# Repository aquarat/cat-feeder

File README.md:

# Cat feeder

An easy-clean, screwless, refrigerated rotary feeder. **Early mechanical and
thermal prototype**, developed from [the original brief](initial-design-brief.md)
and the owner's subsequent decisions in [the project KB](kb/README.md).

Twelve 40 mL portions sit in a lift-out tray. A stepper advances the tray 30°
at a time under a fixed opening in the lid. Thermoelectric coolers chill the
air beneath the tray. The lid hinges open and the tray lifts out for washing
without tools. The prototype is printed in PETG on a Bambu A1 Mini.

| | |
|:---:|:---:|
|  |  |
| **Opened:** twelve compartments in four lift-out sectors on a keyed hub | **Exploded:** lid, tray, plenum deck and body |
|  |  |
| **Section:** tray over the cold-air plenum and equipment bay | **Internals (deck hidden):** TEC stacks, [controller cards](electronics/d34/README.md) and modelled harness |

<p align="center">
  
  <br><em>D34 control card, one of three hand-soldered through-hole boards.</em>
</p>

*These are renders of the CAD model for the
[cold-air plenum study](kb/plenum-cad.md) (D35, still being compared). They
are not photographs: nothing has been built or tested yet. Refresh them with
`bash scripts/export_plenum.sh && bash scripts/readme_images.sh`.*

**[Product-linked BOM](BOM.md)** — UK-oriented sourcing, trial/full quantities,
observed prices and fit dependencies. Start with one thermal wedge; see the
[sourcing evidence](kb/sourcing.md) for outstanding component choices.
The [TEC control recommendation](kb/tec-control.md) identifies a CP60440 sample
and DPS5005 bench regulator, with conditional three-series/four-parallel scaling.
The [PCB assembly review](kb/pcb-assembly.md) recommends JLCPCB Economic as the
first turnkey controller-board route. The [crescent controller draft](kb/pcb-design.md)
has passed independent review.
The [PCB supports and removable sink cradles](kb/pcb-packaging.md) are integrated.
Subsequent [electrical simulations and regression tests](kb/pcb-simulation.md)
identify regulator thermal, motor-supply ringing and interface limits requiring
qualification; no powered hardware or application firmware has been tested.

> **2026-10-25:** a [five-reviewer general review](kb/review-2026-10-25.md) found
> blockers in both PCB revisions and thermal/drag limits in the direct-contact
> concept. Do not quote the prepared JLCPCB project. Latest decisions: 24 V
> mains brick, electronics inside the case, a hand-soldered through-hole
> controller variant, and an exploratory cold-air plenum
> ([thermal](kb/plenum-thermal.md), [CAD study](kb/plenum-cad.md), [sizing](kb/plenum-sizing.md); [D32–D37](kb/decisions.md)). D34 controller cards:
> [electronics/d34](electronics/d34/README.md), [KB](kb/d34-controller.md).
> Plenum views: `bash scripts/export_plenum.sh` → `build/plenum/preview/`.

## Current direction

- **316 mm nominal body**, 280 mm rotating tray, twelve 40 mL working portions.
- Four lift-out tray quadrants, three rounded wedge bowls each. Every bowl is
  continuous; joins are outside the food cavities. Nominal floor **1.2 mm**,
  bowl depth **16 mm**, plan corner radius **5 mm**, floor fillet **3 mm**.
- A broad, uniquely keyed **axial drive coupling** on the stepper. Lift the
  carrier and tray straight off; no shaft screw, nut or fastening operation.
  This resembles a large gear but does not provide gear reduction.
- Rear pin hinge and **one front-right clip** reuse the rowing IMU mechanisms.
  Filament offcuts form the pins. The enlarged lid needs its own load/fit trial.
- **18 mm printed insulation deck**, low-infill enclosed construction; no foam.
- **Domed lid with a broad, gently sloping feeding recess**. The mouth edge
  stands just 2.8 mm above the tray rim. The rest of the lid grows thicker.
- **12 mm cylindrical walls**, with honeycomb specified by Bambu print settings.
  CAD describes the envelopes; there are no modelled honeycomb cavities.
- **Enclosed, slotted underside** and numerous narrow vertical side vents.
  Floor-rooted seats, guides and bounded electrical bays load from the top.
- **Twelve distributed cooling positions**, one beneath each parked portion,
  replacing the custom circular aluminium plate. The current layout reserves
  40 mm TECs directly contacting the PETG tray and individual heat sinks. Final TEC size,
  count and power depend on the thermal study and a single-position experiment.
- One common fan and local thermostatic control. The original 100 W USB-C supply
  remains a candidate, not a proven budget for this revised cooling layout.
- Bottom **120 mm upward-blowing axial fan**, with a printed inlet skirt,
  enlarged floor intake and raised side exhaust band. See [airflow study](kb/airflow.md).

## Files and views

| File | Purpose |
| --- | --- |
| `cad/parameters.scad` | Dimensions, provisional component envelopes and clearances |
| `cad/feeder.scad` | Parametric assembly, section, exploded view and prototype parts |
| `cad/internals.scad` | Floor supports, removable motor bridge, board bays and loading paths |
| `cad/pcb_mount.scad` | Crescent PCB edge seat, lift-out sink cradles and staged loading paths |
| `docker/openscad.Dockerfile` | Headless build of the pinned public OpenSCAD fork |
| `scripts/openscad.sh` | Run OpenSCAD in that Docker image, with this project mounted |
| `scripts/fetch_references.py` | Fetch the manufacturer datasheets listed in `references.json` |
| `scripts/export.sh` | Export prototype STLs and current PNG views |
| `scripts/check_mesh.py` | Actual mesh topology, connectedness, bed fit and bowl capacity |
| `kb/` | Decisions, evidence, open questions and handover notes |
| `thermal/` | Thermal modelling tools and their results |
| `slicer/` | Editable Bambu project plate generation and print settings |
| `cad/lib/` | Hinge/clip mechanisms and edge helpers vendored from upstream ([provenance](#provenance)) |

Generated outputs are in `build/stl/`, `build/preview/` and
`build/geometry-report.json`. `capacity.stl` is the **empty volume of one bowl**
for measurement, not a printable part. Colours in assembly views distinguish
components; the rectangular heat sinks and fan are packaging envelopes.

[Opened assembly](build/preview/opened.png) ·
[Section](build/preview/section.png) ·
[Feeding recess](build/preview/access.png) ·
[Component bays](build/preview/loading.png) ·
[Underside](build/preview/underside.png) ·
[Fan inlet coupon](build/preview/fan_inlet_coupon.png)

The bowl capacity is **53.20 mL**. The full lid and shell remain assembly-scale
models requiring printable subdivision. See [validation details and limits](kb/validation.md)
for the tested revision and [the drop-in layout](kb/drop-in-layout.md) for assembly order.
The current thirteen prototype meshes and 44 nominal clearance checks pass; eleven
editable, unsliced Bambu projects are available in [slicer/plates](slicer/plates/).
The PCB fit study adds 21 passing checks against the integrated shell.

The [earlier thermal study](kb/thermal-model.md) identifies lateral heat spreading
as an unresolved issue with small cold footprints. The latest prototype removes
the small aluminium caps and tests direct TEC-to-PETG contact. Start with one
instrumented wedge and its insulated cover before scaling to twelve sites.
The [direct-contact comparison](kb/direct-contact-thermal.md) finds only about
0.3–0.4°C higher mean food-layer temperature without the small caps under matched
ideal cold-face conditions; contact gaps matter more. These are simulations.

## Reproduce

The CAD scripts run a headless OpenSCAD in Docker. Build the image once
(20–40 minutes; it compiles the pinned
[public OpenSCAD fork](https://github.com/aquarat/openscad), which adds the
experimental `geometry-metrics` checks):

```sh
docker build -t cat-feeder-openscad -f docker/openscad.Dockerfile docker
```

Manufacturer datasheets are not redistributed. Fetch them to the paths the
documentation cites (hash-checked against the revisions used):

```sh
python3 scripts/fetch_references.py
```

Export and check:

```sh
bash scripts/export.sh
python3 scripts/check_mesh.py
bash scripts/check_clearances.sh
python3 slicer/make_plates.py --require-part lid_access_coupon --require-part motor_bridge --require-part fan_inlet_coupon --require-part pcb_cradle --require-part pcb_mount_coupon
python3 slicer/make_plates.py --verify-only
```

Editable **unsliced** Bambu projects are written to `slicer/plates/`. Open them
as projects and retain their settings, then slice in Bambu Studio. No GUI or
slicer executable is required to generate these files here; no print G-code
is claimed. See [printing notes](kb/printing.md).

For one part or a parameter variation:

```sh
mkdir -p build/stl
bash scripts/openscad.sh --backend=Manifold --export-format binstl \
  -D 'part="sector"' -D 'floor_t=1.6' \
  -o build/stl/sector-thicker.stl cad/feeder.scad
```

## Prototype print order

1. **One tray sector**: check 40 mL filling, cat access, leakage and cleaning.
   Print flat underside down. The dry inner flange is on the bed too.
2. **Drive and hub**: check the measured motor shaft, master-tooth engagement,
   vertical removal and torque. Nominal sliding clearance is 0.3 mm per side;
   the provisional 5 mm D shaft has a separate close fit. The drive's blind
   socket seats on the shaft tip, its shoulder supports the hub, and two tabs
   provide a finger grip. The motor envelope assumes a 28 mm body/18 mm shaft.
3. **Rowing closure coupons and clip**: reproduce the actual hinge/catch
   interfaces. These are upstream coupons, not a full-size lid strength test.
4. **One insulation quadrant**: cold face down, as exported. Start with
   0.8 mm skins and 5–8% infill; inspect closure of the infill and print accuracy.
   This is a packaging coupon; module retention and moisture detailing follow
   the selected cooling cartridge.
5. **Insulation coupon**: a plain 60 mm square envelope. Apply the Bambu
   honeycomb/skin settings and inspect the generated infill and roof layers.
6. **Feeding-access coupon**: the actual front section of the sloped lid,
   including its thin opening lip. Check access and whisker clearance over a tray.
7. **Motor bridge**: its 2 mm bearing lip sits 1 mm above the fan; check seating
   on the four floor posts and the actual motor before a full loaded build.
8. **Fan-inlet coupon**: trial the actual enlarged floor slots, 2 mm-high inlet
    skirt and corner seats with the selected 120 mm fan before printing the shell.
9. **PCB mount coupon and two cradles**: check the edge seat, locating sockets,
   actual solder tails and driver stack. The cradle project contains one copy;
   print two for the assembly. Connect terminal wires after seating the PCB.

PETG, 0.4 mm nozzle and 0.2 mm layers are the initial process assumptions.
Use solid floors/perimeters on food parts; low infill applies to insulation,
not liquid-retaining walls. Rounded geometry helps washing, but does not by
itself establish FDM surface cleanability or food-contact suitability. Treat
these as water/fit prototypes until the material and cleaning process are settled.

## What is modelled versus resolved

The tray, drive, closure coupons, feeding-access coupon and removable motor
bridge have exportable prototype geometry. Mesh checks establish printable size
and closed surfaces, not physical fit, lifetime or liquid tightness.

The **full shell and lid are assembly studies**, not final A1 Mini prints.
Their quadrant joints, full-size lid support/stop, anti-lift retention, fan duct,
indexing sensor, condensate management and cartridge clamps still need detail.
Bounded electronics bays and floor-supported component seats are present. The
crescent uses its actual PCB outline with provisional component/harness heights;
the other three pockets remain unselected module allowances. The deck needs final quadrant joining and
cartridge retention features. Final hardware dimensions and firmware pinout
are not frozen.

The direct-contact prototype needs repeatable TEC face height and hot-side
contact with its sink. The deck carries the tray around each exposed cold face;
physical flatness/contact and sliding drag need a trial. Small aluminium caps
are removed. A proven long-life spring clamp is not a prerequisite for testing
the concept, but the final hot-side retention method remains to qualify.

Daily operation should be: release the clip, open lid, lift the complete tray by
its carrier, separate quadrants for washing/refilling, reseat and close. The
hub's unique key restores mechanical phase; starting a new food batch must
still reset the serving count. The four identical tray quadrants can otherwise
be exchanged, so lifting/reloading during an active batch requires rechecking it.

## Provenance

`cad/lib/` holds three OpenSCAD files vendored from the author's rowing-computer
project, unchanged apart from include paths: `sensor.scad` (the rear pin hinge
and clip mechanisms, rowing revision `5eb1d5683712bf8eaba0b004c4f59e09f8ab5160`)
and `edges.scad`/`dfm.scad`, which are also published in the
[OpenSCAD fork](https://github.com/aquarat/openscad) at
`12b187123519cd9050ce37341aefaa3e31ced1f7`.

This repository is a published snapshot of the project's working repository.
Issues and pull requests are welcome; accepted changes are applied upstream
and appear here in the next snapshot.

## Licence

Copyleft throughout: CERN-OHL-S-2.0 for hardware designs, GPL-3.0-or-later for
software, CC-BY-SA-4.0 for documentation, plus third-party AGPL/SparkFun files.
See [LICENSE.md](LICENSE.md). This is an untested prototype; no warranty.

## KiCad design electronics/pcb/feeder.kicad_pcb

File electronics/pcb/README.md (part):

# Cat-feeder controller — revision A draft

Editable **KiCad 9** schematic and fully connected, two-layer **shallow crescent PCB, 58.12 × 80 mm bounding box**. Actual area is only **2.17% above the 50 × 80 mm rectangular baseline**. This is a checked design draft, not a fabricated/tested controller. Start with [packaging assumptions/comparison](PACKAGING.md), [design rationale](../../kb/pcb-design.md) and [check results](CHECKS.md).

**D25 HOLD: review corrections are ready for focused independent recheck; supplier-project creation remains prohibited.** [Precise B1/B2/rule-fix record](REVIEW-FIXES.md). Current revision adds R20/R21; all original placements and the outline are preserved.

## Files

| File | Purpose |
|---|---|
| `feeder.kicad_pro`, `feeder.kicad_sch`, `feeder.kicad_pcb` | Open the project in KiCad 9; current editable design |
| `feeder.pretty/`, `fp-lib-table`, `sym-lib-table` | Local footprint copies; schematic embeds its symbols and references standard KiCad 9 symbol libraries |
| `views/schematic.pdf`, `views/feeder.svg` | Current schematic; net-labelled pin stubs carry the electrical connections |
| `views/top.svg`, `views/bottom.svg`, `views/assembly.svg` | Current copper/component views; bottom view is **not mirrored**, seen through the board from above |
| `views/board-only.step`, `views/board-envelope.stl`, `outline-study.json` | Curved-outline mechanical handoff; coordinate systems and omitted geometry in [PACKAGING.md](PACKAGING.md) |
| `design-bom.csv`, `connectivity.json`, `schematic-netlist.xml` | Full design BOM and connectivity |
| `assembly-bom.csv`, `assembly-cpl.csv` | **36 SMT placements only**, grouped supplier BOM and placement input |
| `assembly-bom-all.csv`, `assembly-cpl-all.csv` | **54-part mixed SMT+THT draft** with corrected body centroids; supplier zero angles pending |
| `quotation-bom-all.csv` | All **54 parts**, including 18 THT parts for later mixed-process quotation scope |
| `assembly.py`, `assembly-reconciliation.json` | Exact-code body offsets, all 54 placements/pads and orientation landmarks |
| `REVIEW-FIXES.md`, `review-fix-validation.json` | B1/B2 provenance, placement preservation and focused-recheck handoff |
| `manufacturing/`, `manufacturing-draft.zip` | Current nine Gerbers, job file and Excellon drill file |
| `stock-evidence.json` | Timestamped public JLC inventory fields, URLs and response hashes |
| `erc.rpt`, `drc.rpt`, `validation.json`, `checksums.json` | Checks against these files, not an earlier routing revision |
| `generate.py`, `outline.py`, `route.py`, `finish_route.py`, `export.py` | Source generator, curved outline, route import/finishing and fail-on-violation export |
| `feeder-unrouted.kicad_pcb`, `feeder.dsn`, `feeder.ses` | Placement and offline routing intermediate files; open **feeder.kicad_pcb** for the finished draft |

Gerber, drill and CPL share the lower-left board-bounding-box origin: X right, Y up, at KiCad **(41.88227, 130) mm**. The CAD board occupies approximately X41.882–100/Y50–130 mm. CPL now uses **component-body centroids**, with explicit offsets for all 18 THT parts rotated before origin conversion. Centred SMT origins are preserved. Angles remain native KiCad; supplier library zero-angle/pad alignment remains pending. See [reconciliation](REVIEW-FIXES.md#b2-true-body-centroid-export).

## Assembly scope

- SMT: ESP32-WROOM-32E-N4, AP2112K-3.3 LDO, two UART gates, fan transistor and passives. All selected SMT codes had positive direct JLC stock on 2026-10-24.
- THT: 3 Phoenix screw terminals, 2 A4988 sockets, 12 other headers and 1 motor bulk capacitor. All have exact stocked catalogue candidates; JLC marks them `manualWeld`. For fitted terminals/headers use the **`-all` BOM/CPL pair** and quotation scope, rather than the SMT-only pair. See [sourcing](SOURCING.md) and [assembly-service research](../../kb/pcb-assembly.md).
- Separate integration: A4988 carrier, external 5 V/12 V converters, protected 20/24 V motor source, DPS5005, TEC power switching/interlock, sensors, fan and all harnesses. The A4988 carrier is **not** in the assembler BOM.
- Board specification for quotation: 2 layers, nominal 1.6 mm FR-4, nominal 1 oz copper, solder mask both sides, top silkscreen, no mechanical mounting holes. No current rating is inferred from this specification.
- Target service: Economic PCBA, single-side SMT+THT, **minimum two assembled boards**. Curved-board handling rails/panelisation and exact part eligibility remain supplier questions. Public stock evidence remains the source; D25 blocks project preparation until focused recheck passes.
- Twelve 0.2 mm plated holes in the ESP32 thermal land need assembler review for drilling, paste and solder wicking. Routing vias are 0.6/0.3 mm. Confirm programming/test provision and module handling with the assembler at quotation stage.

## Connector pinout

Pin numbers are the PCB pad numbers; pin 1 has the square pad. Header pin 1 is normally uppermost in the top view; J12/J13 run left-to-right. Verify harness numbering rather than relying on wire colour. All grounds on this board are common.

| Ref | Pins in numerical order | Notes |
|---|---|---|
| J1 | 1 VMOT, 2 GND | Protected **20–24 V** motor input; not TEC power |
| J2 | 1 GND, 2 +5 V, 3 +12 V | External regulated rails; never put motor voltage here |
| J3 | 1 GND, 2 +12 V, 3 TACH, 4 PWM | Generic 2.54 mm header, **not a keyed PC-fan receptacle**; adapter harness required |
| J4/J5 | 1 GND, 2 DQ, 3 +3.3 V | Powered DS18B20 probes; shared 1-Wire bus, single 4.7 kΩ pull-up |
| J6 | 1 GND, 2 INDEX, 3 +3.3 V | 3.3 V-compatible optical module/open-collector input |
| J7 | 1 GND, 2 HOME, 3 +3.3 V | Independent home sensor; 10 kΩ pull-up |
| J8 | 1 GND, 2 +3.3 V, 3 SDA, 4 SCL | Optional I²C; 4.7 kΩ pull-ups fitted |
| J9 | 1 GND, 2 **DPS RX**, 3 **DPS TX** | Names are from the DPS's perspective; no DPS VCC connection |
| J10 | 1 GND, 2 TEC_EN | Default-low **3.3 V logic only**; requires separately designed compatible enable/interlock stage |
| J11 | 1 GND, 2 ESP TX0, 3 ESP RX0, 4 +3.3 V reference | External 3.3 V UART adapter; cross adapter TX/RX; pin 4 is a reference, not a 5 V input |
| J12 | 1 BOOT/GPIO0, 2 GND | Short while resetting to enter ROM download mode |
| J13 | 1 EN, 2 GND | Momentarily short to reset |
| J14 | EN/GND, MS1/+3V3, MS2/+3V3, MS3/+3V3, RESET/MOTOR_RUN, SLEEP/MOTOR_RUN, STEP, DIR | A4988 control row, pin 1→8 |
| J15 | VMOT, GND, 2B, 2A, 1A, 1B, VDD/+3V3, GND | A4988 power row, pin 1→8; 15.24 mm from J14 |
| J16 | 1 M1A, 2 M1B | Motor winding 1 |
| J17 | 1 M2A, 2 M2B | Motor winding 2 |

J14 and J15 are for the standard **Pololu-layout A4988** carrier viewed from its component side, VMOT at the upper-right. Confirm a purchased clone's pinout before insertion. DRV8825 or other drop-ins have not been qualified. Set the carrier's current limit for the actual motor; disconnect power before changing motor wiring.

## Firmware interface and reset behaviour

No firmware is supplied. GPIO numbers below are ESP32 GPIOs, not WROOM pad numbers.

| GPIO | Function | Behaviour/requirement |
|---|---|---|
| 16 / 17 | DPS RX / TX | UART through separate SN74LVC1G125 gates |
| 13 | UART_OEn | 10 kΩ pull-up disables both gates during reset; drive low only after qualification/startup |
| 18 / 19 | STEP / DIR | 100 kΩ pull-downs; A4988 fixed 1/16 microstepping |
| 23 | MOTOR_RUN | 10 kΩ pull-down; RESET and SLEEP low at reset; drive high, then observe carrier wake-up delay before stepping |
| 25 | TEC_EN | 10 kΩ pull-down; active high only for an external stage designed for this input |
| 26 | FAN_PWM_GPIO | MMBT3904 open-collector output, **inverting**; use nominal 25 kHz and account for inversion |
| 27 | 1-Wire DQ | Powered DS18B20 bus |
| 32 / 33 | INDEX / HOME | 10 kΩ pull-ups; debounce/filter in firmware |
| 34 | FAN_TACH | Input-only, external 10 kΩ 3.3 V pull-up and 1 kΩ series resistor; open-collector tach expected |
| 35 | BUS_SENSE | ADC1, 100 kΩ/10 kΩ divider plus 100 nF: nominal bus/11 (24 V→2.18 V); calibrate attenuation/gain |
| 21 / 22 | SDA / SCL | Optional 3.3 V I²C |
| 0 / EN | BOOT / RESET | 10 kΩ pull-ups; EN has 1 µF delay capacitor |
| 1 / 3 | UART0 TX / RX | Programming/diagnostics on J11 |

With the MCU reset, Q1 is off so the fan's PWM pin is released high; a conforming four-wire fan should run at full speed. This depends on the chosen fan's internal pull-up. Fan motor power is always connected to +12 V; this circuit cannot switch it off independently.

The DPS RX buffer input tolerates up to 5.5 V; its output to the ESP32 is 3.3 V. Board TX is buffered 3.3 V through 1 kΩ, **not a 5 V translator or RS-232 interface**. Check the exact DPS hardware's UART voltage/threshold, ground relationship, protocol and power-order behaviour. OE disables board drivers; it is not galvanic isolation. **J10 is not a verified DPS5005 enable-pin connection**, and default-low logic does not by itself disconnect TEC power. Implement and test an external fail-off power stage and overtemperature/fan-failure shutdown before unattended thermal trials.

R20 = 10 kΩ pulls U3.2/DPS_TX to +3V3 during ESP reset. R21 = 10 kΩ pulls U4.2/DPS_TX_EXT to GND with DPS absent/off; active DPS TX must drive 0.33 mA at 3.3 V or 0.50 mA at 5 V. Keep OE disabled when DPS is absent/off. OE bias alone does not bias CMOS data inputs.

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
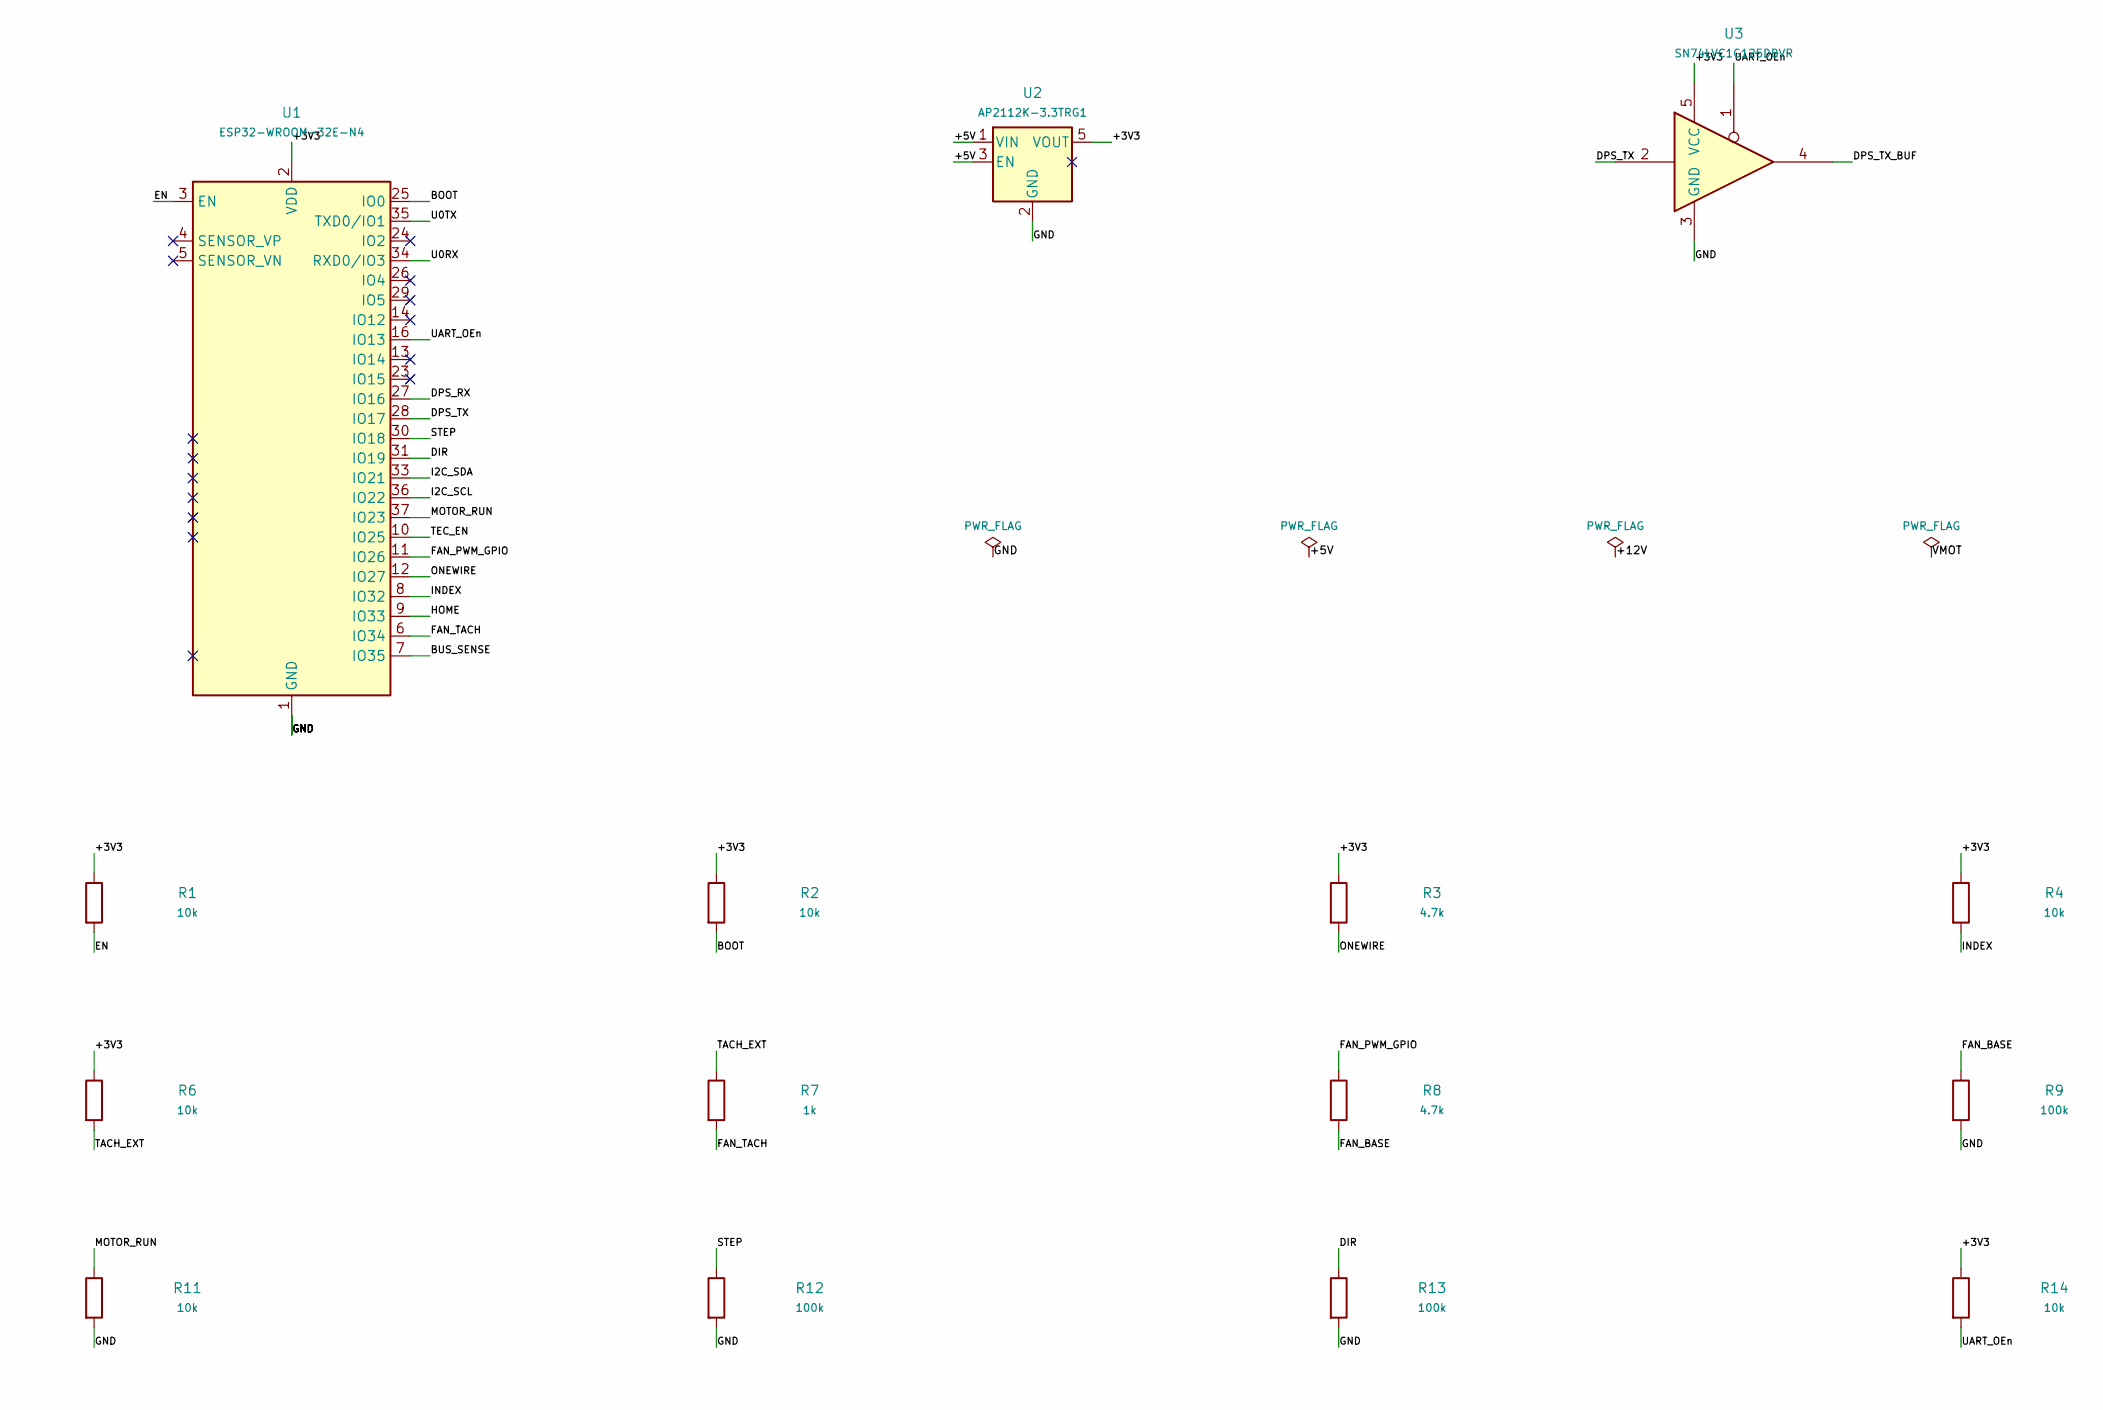
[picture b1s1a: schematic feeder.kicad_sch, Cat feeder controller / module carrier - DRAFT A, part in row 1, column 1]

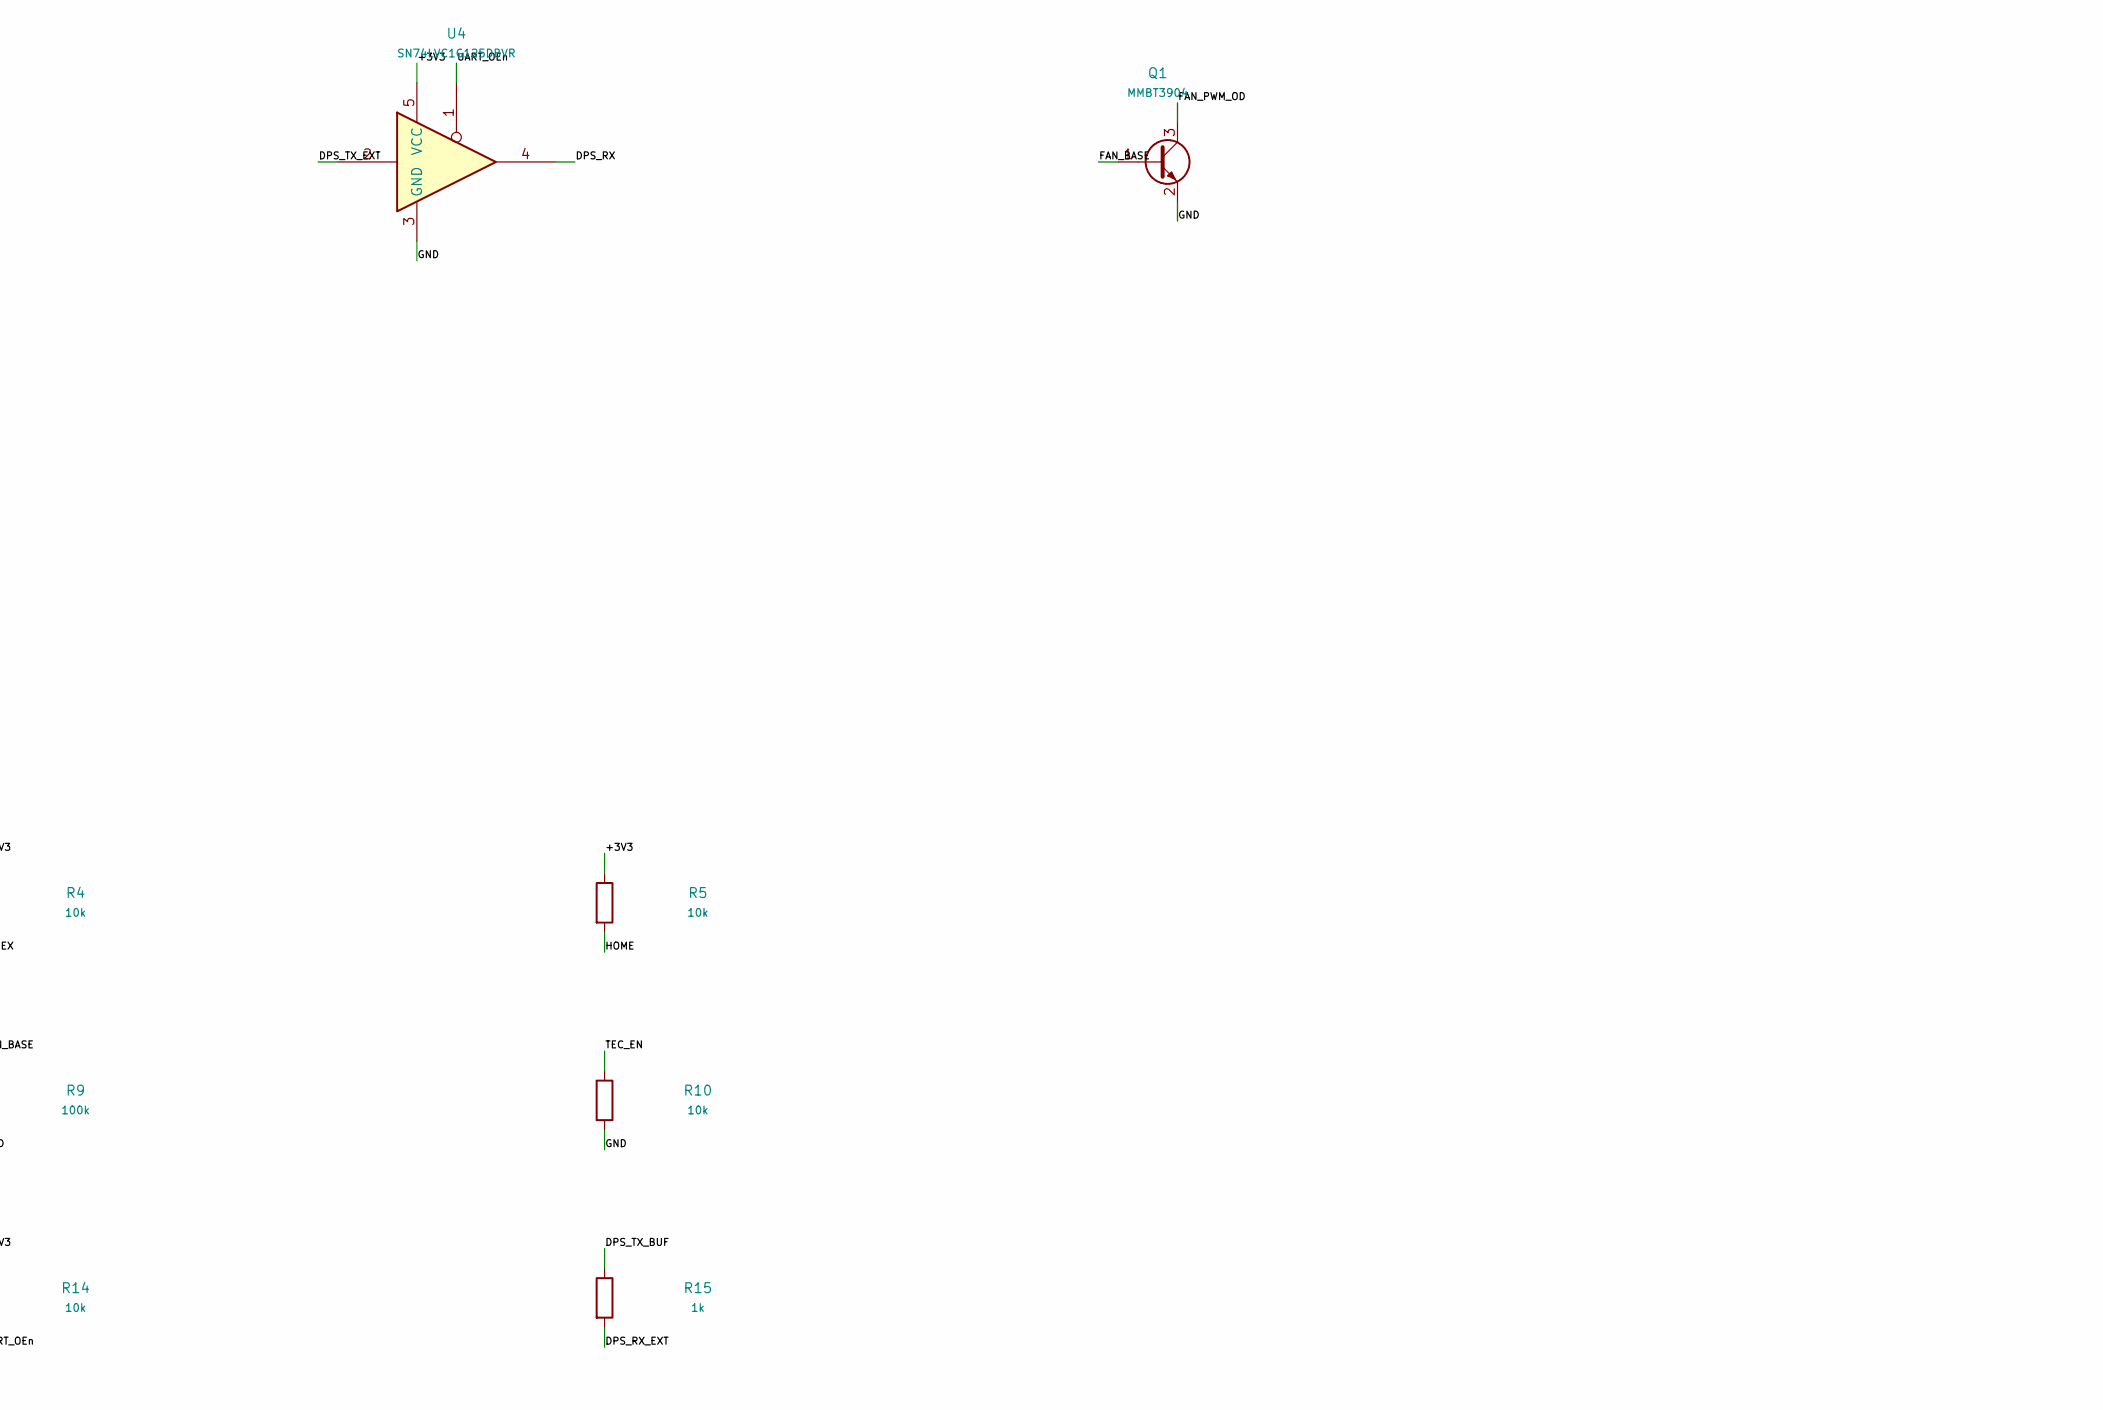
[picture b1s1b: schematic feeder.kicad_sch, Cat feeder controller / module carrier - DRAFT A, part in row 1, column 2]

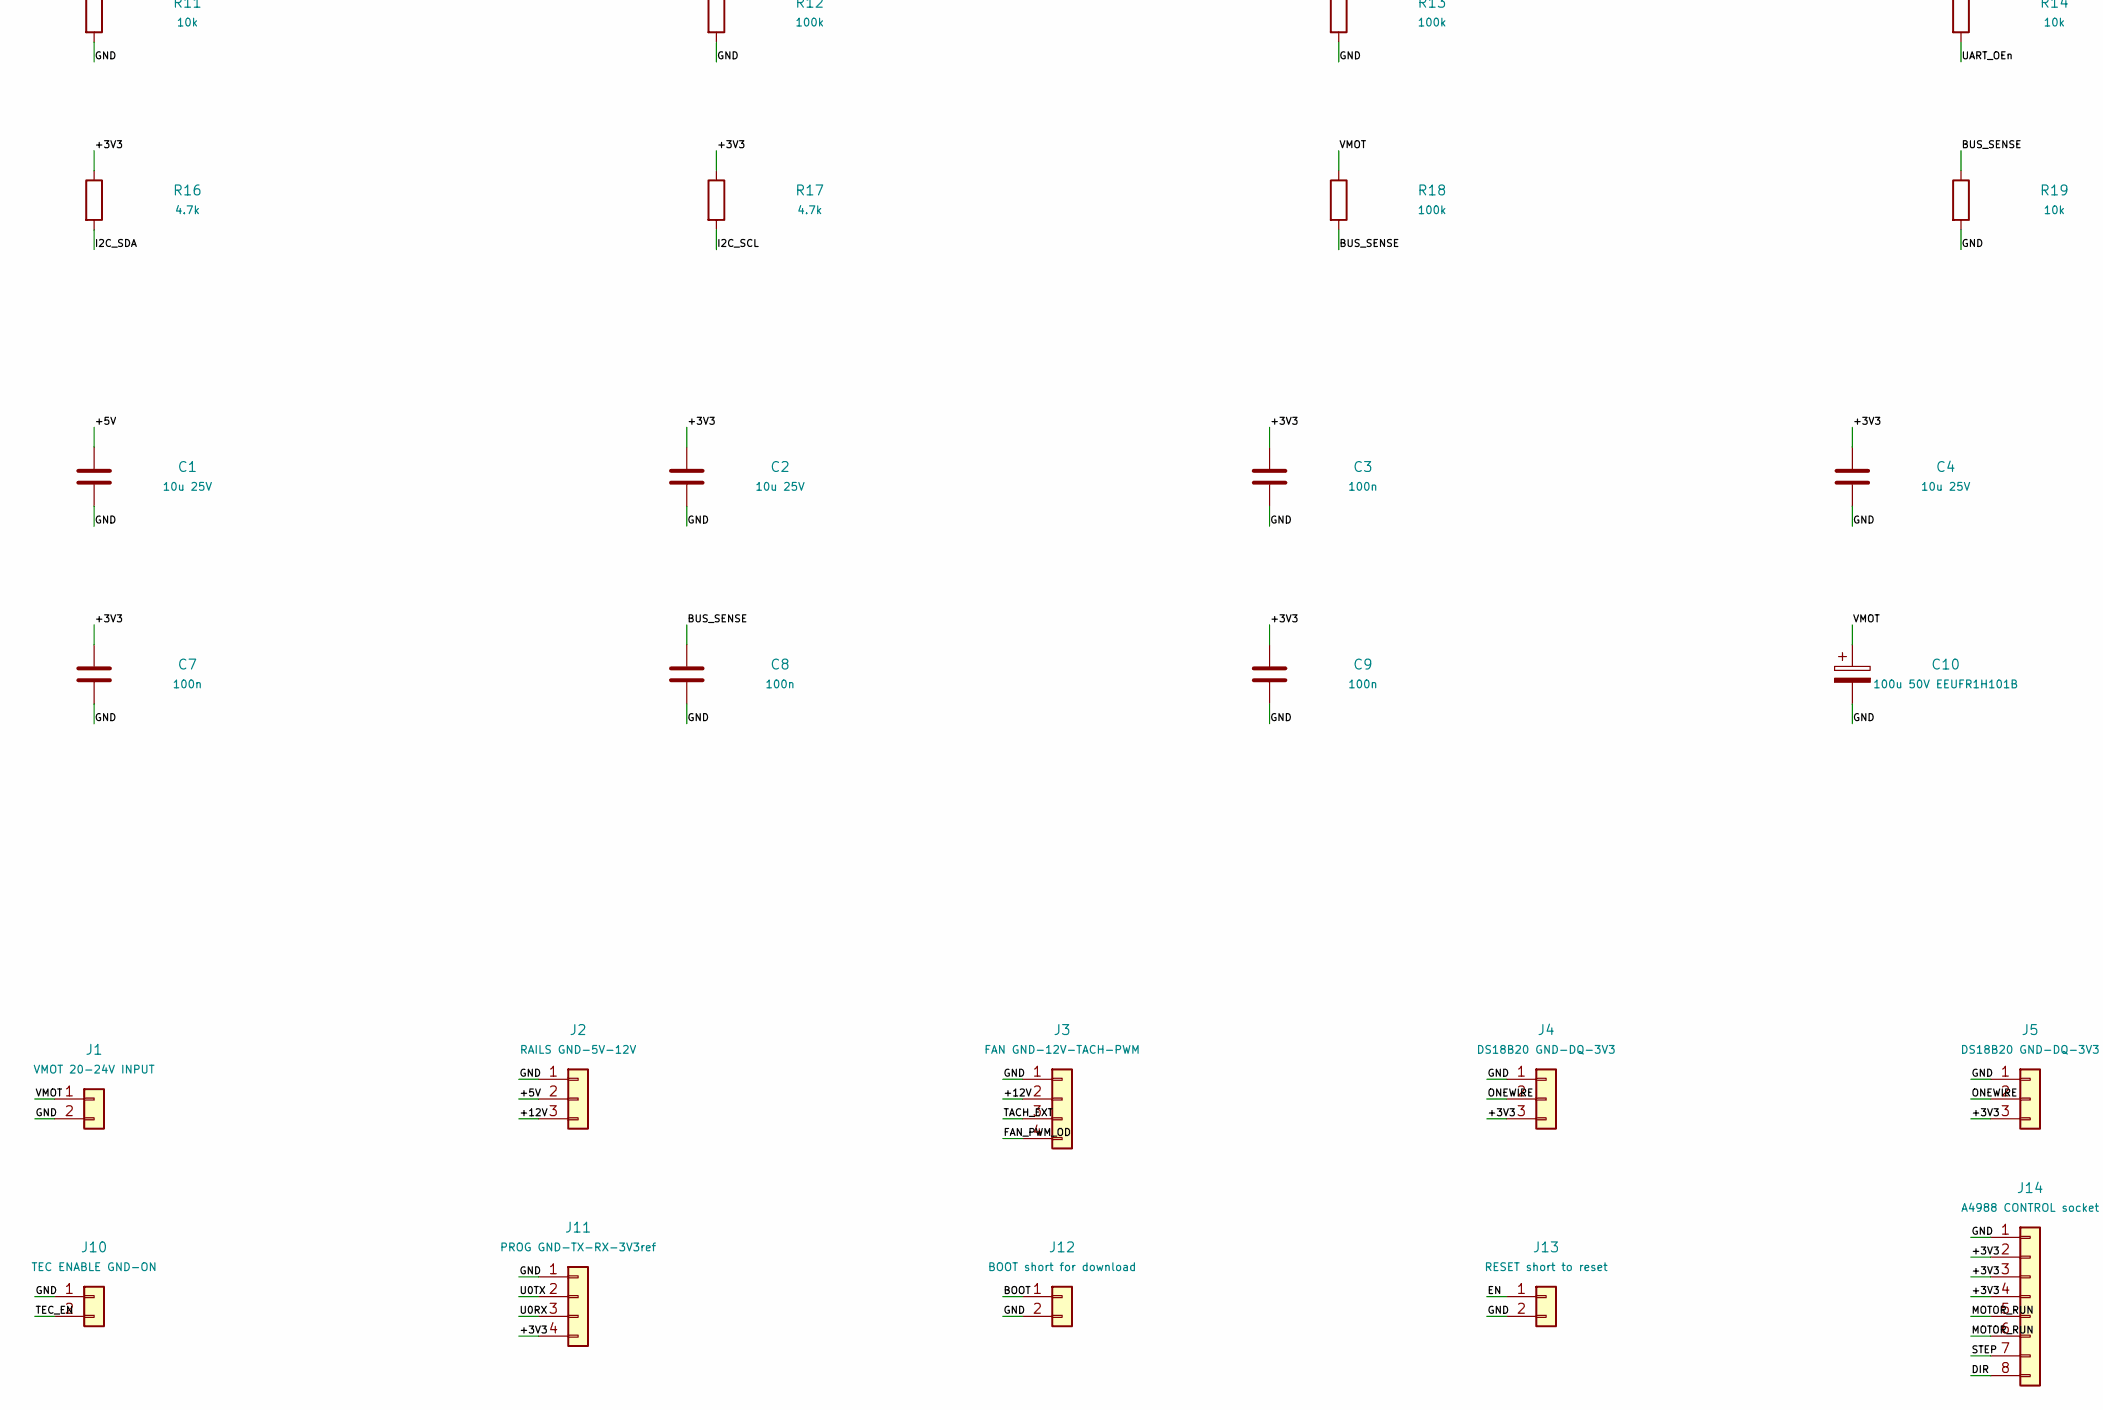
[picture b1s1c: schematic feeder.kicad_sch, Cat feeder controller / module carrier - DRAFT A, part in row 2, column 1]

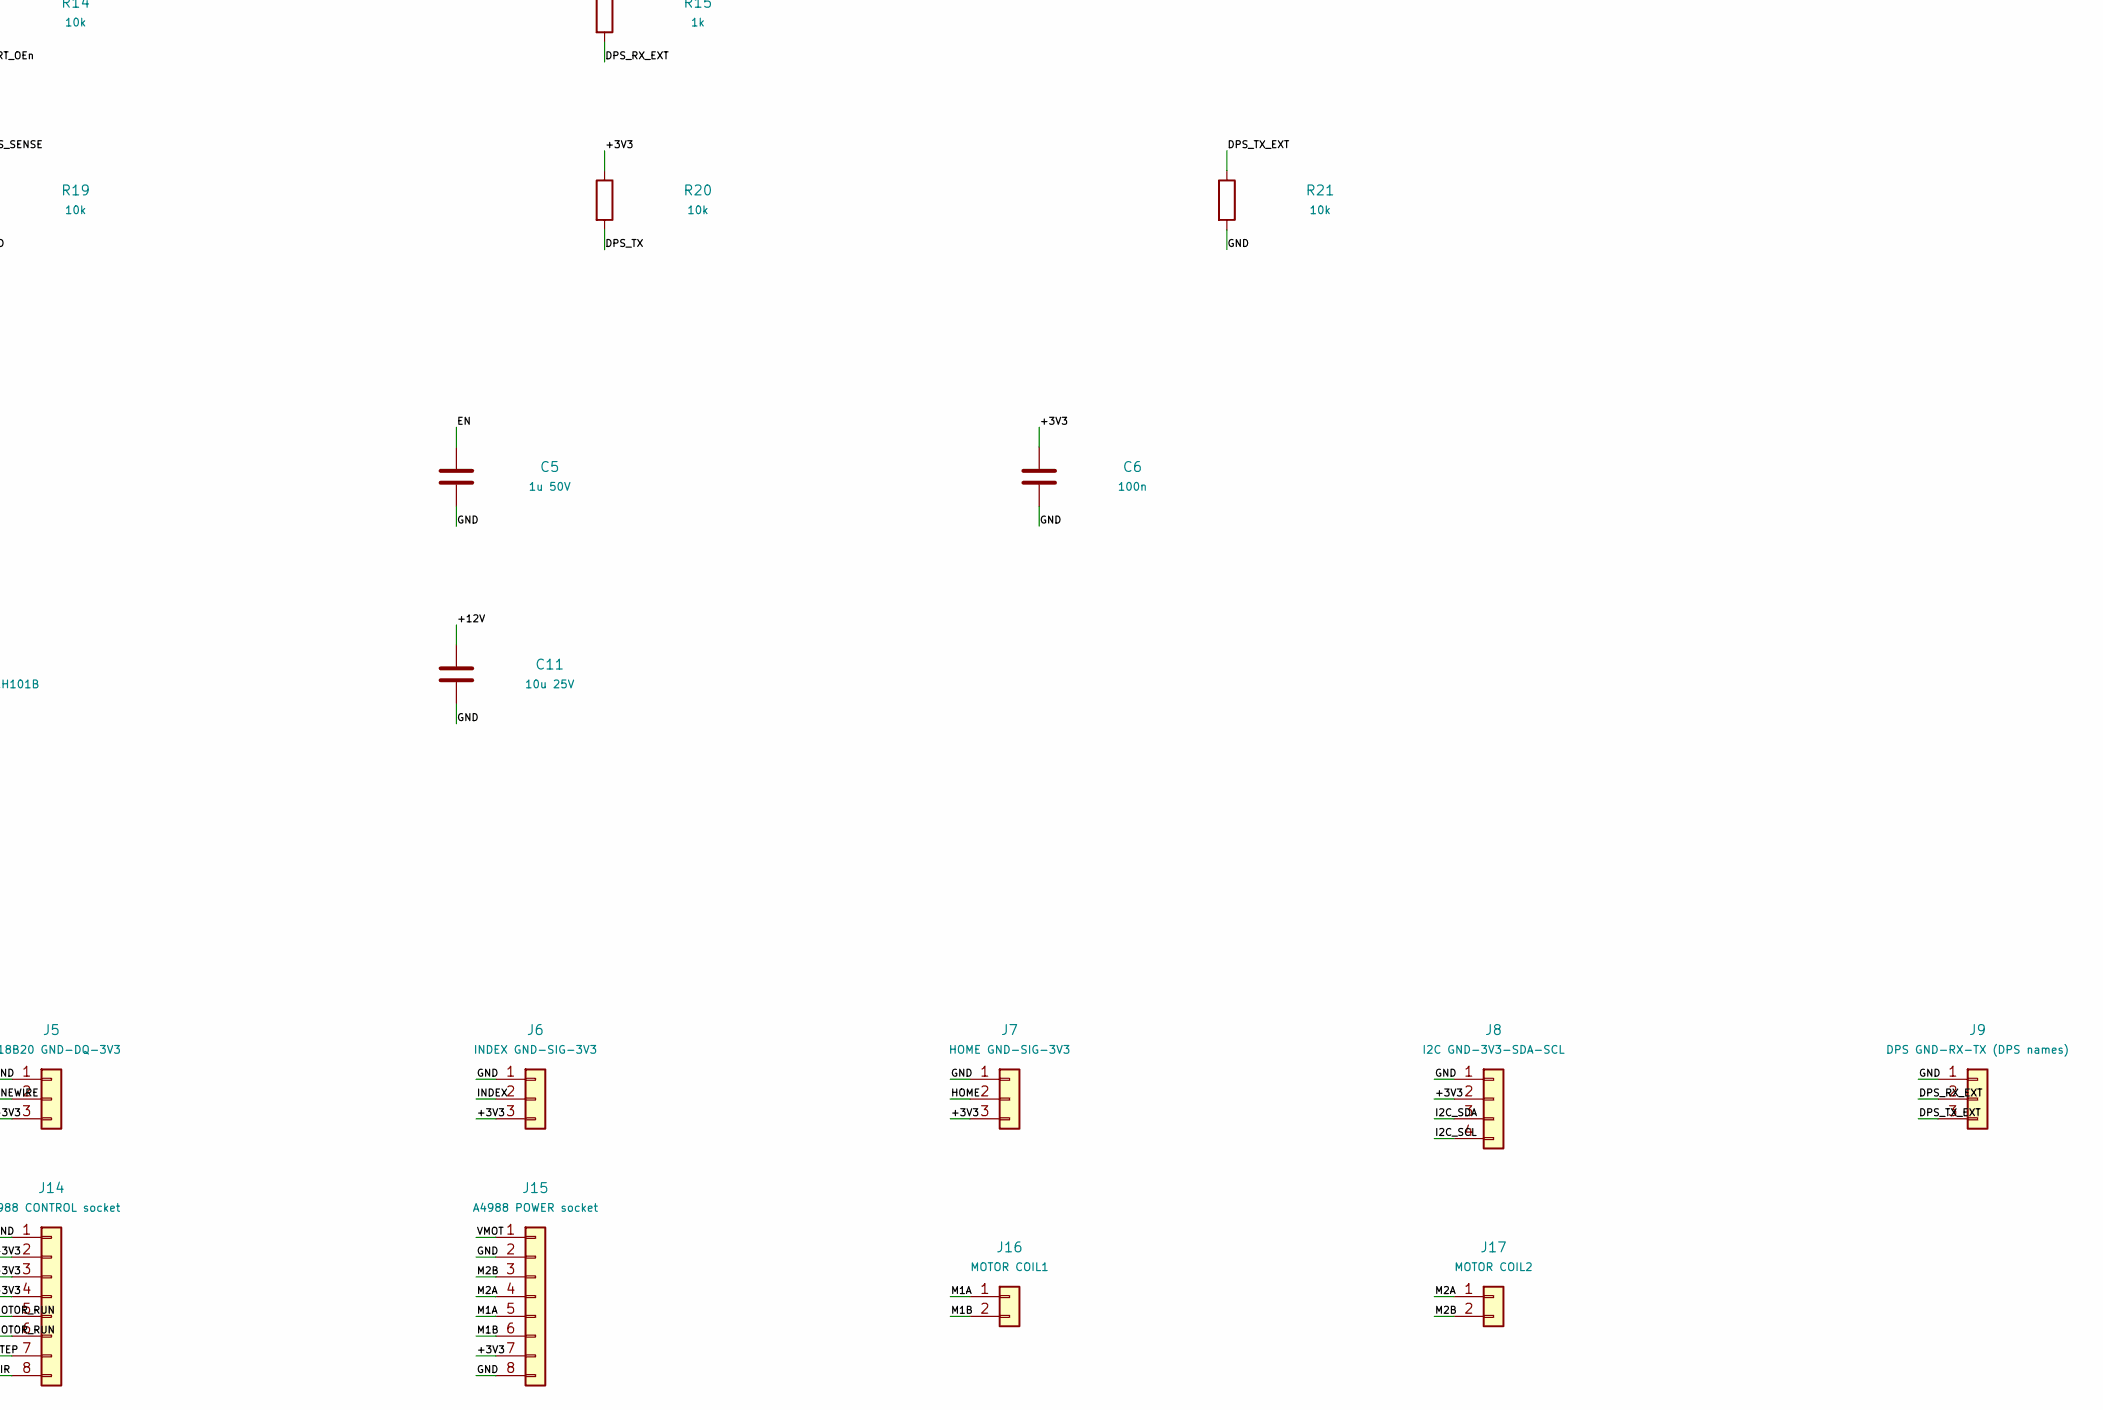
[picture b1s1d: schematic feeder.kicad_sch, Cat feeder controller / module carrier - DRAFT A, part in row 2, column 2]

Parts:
C1, C2, C4, C11: 10u 25V; C_0805_2012Metric; LCSC C15850
C3, C6, C7, C8, C9: 100n; C_0603_1608Metric; LCSC C14663
C5: 1u 50V; C_0603_1608Metric; LCSC C15849
C10: 100u 50V EEUFR1H101B; CP_Radial_D8.0mm_P5.00mm; LCSC C713402
J1: VMOT 20-24V INPUT; TerminalBlock_Phoenix_MKDS-1,5-2-5.08_1x02_P5.08mm_Horizont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; LCSC C5183929
J2: RAILS GND-5V-12V; PinHeader_1x03_P2.54mm_Vertical; LCSC C49257
J3: FAN GND-12V-TACH-PWM; PinHeader_1x04_P2.54mm_Vertical; LCSC C5116483
J4, J5: DS18B20 GND-DQ-3V3; PinHeader_1x03_P2.54mm_Vertical; LCSC C49257
J6: INDEX GND-SIG-3V3; PinHeader_1x03_P2.54mm_Vertical; LCSC C49257
J7: HOME GND-SIG-3V3; PinHeader_1x03_P2.54mm_Vertical; LCSC C49257
J8: I2C GND-3V3-SDA-SCL; PinHeader_1x04_P2.54mm_Vertical; LCSC C5116483
J9: DPS GND-RX-TX (DPS names); PinHeader_1x03_P2.54mm_Vertical; LCSC C49257
J10: TEC ENABLE GND-ON; PinHeader_1x02_P2.54mm_Vertical; LCSC C27985187
J11: PROG GND-TX-RX-3V3ref; PinHeader_1x04_P2.54mm_Vertical; LCSC C5116483
J12: BOOT short for download; PinHeader_1x02_P2.54mm_Vertical; LCSC C27985187
J13: RESET short to reset; PinHeader_1x02_P2.54mm_Vertical; LCSC C27985187
J14: A4988 CONTROL socket; PinSocket_1x08_P2.54mm_Vertical; LCSC C27438
J15: A4988 POWER socket; PinSocket_1x08_P2.54mm_Vertical; LCSC C27438
J16: MOTOR COIL1; TerminalBlock_Phoenix_MKDS-1,5-2-5.08_1x02_P5.08mm_Horizont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; LCSC C5183929
J17: MOTOR COIL2; TerminalBlock_Phoenix_MKDS-1,5-2-5.08_1x02_P5.08mm_Horizont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; LCSC C5183929
Q1: MMBT3904; SOT-23; LCSC C20526
R1, R2, R4, R5, R6, R10, R11, R14, R19, R20, R21: 10k; R_0603_1608Metric; LCSC C25804
R3, R8, R16, R17: 4.7k; R_0603_1608Metric; LCSC C23162
R7, R15: 1k; R_0603_1608Metric; LCSC C21190
R9, R12, R13, R18: 100k; R_0603_1608Metric; LCSC C25803
U1: ESP32-WROOM-32E-N4; ESP32-WROOM-32E; LCSC C701341
U2: AP2112K-3.3TRG1; SOT-23-5; LCSC C51118
U3, U4: SN74LVC1G125DBVR; SOT-23-5; LCSC C23654

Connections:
/+3V3: C2.1, C3.1, C4.1, C6.1, C7.1, C9.1, J4.3, J5.3, J6.3, J7.3, J8.2, J11.4, J14.2, J14.3, J14.4, J15.7, R1.1, R2.1, R3.1, R4.1, R5.1, R6.1, R14.1, R16.1, R17.1, R20.1, U1.2 (VDD), U2.5 (VOUT), U3.5 (VCC), U4.5 (VCC)
/+5V: C1.1, J2.2, U2.1 (VIN), U2.3 (EN)
/+12V: C11.1, J2.3, J3.2
/BOOT: J12.1, R2.2, U1.25 (IO0)
/BUS_SENSE: C8.1, R18.2, R19.1, U1.7 (IO35)
/DIR: J14.8, R13.1, U1.31 (IO19)
/DPS_RX: U1.27 (IO16), U4.4
/DPS_RX_EXT: J9.2, R15.2
/DPS_TX: R20.2, U1.28 (IO17), U3.2
/DPS_TX_BUF: R15.1, U3.4
/DPS_TX_EXT: J9.3, R21.1, U4.2
/EN: C5.1, J13.1, R1.2, U1.3 (EN)
/FAN_BASE: Q1.1 (B), R8.2, R9.1
/FAN_PWM_GPIO: R8.1, U1.11 (IO26)
/FAN_PWM_OD: J3.4, Q1.3 (C)
/FAN_TACH: R7.2, U1.6 (IO34)
/GND: C1.2, C2.2, C3.2, C4.2, C5.2, C6.2, C7.2, C8.2, C9.2, C10.2, C11.2, J1.2, J2.1, J3.1, J4.1, J5.1, J6.1, J7.1, J8.1, J9.1, J10.1, J11.1, J12.2, J13.2, J14.1, J15.2, J15.8, Q1.2 (E), R9.2, R10.2, R11.2, R12.2, R13.2, R19.2, R21.2, U1.1 (GND), U1.15 (GND), U1.38 (GND), U1.39 (GND), U2.2 (GND), U3.3 (GND), U4.3 (GND)
/HOME: J7.2, R5.2, U1.9 (IO33)
/I2C_SCL: J8.4, R17.2, U1.36 (IO22)
/I2C_SDA: J8.3, R16.2, U1.33 (IO21)
/INDEX: J6.2, R4.2, U1.8 (IO32)
/M1A: J15.5, J16.1
/M1B: J15.6, J16.2
/M2A: J15.4, J17.1
/M2B: J15.3, J17.2
/MOTOR_RUN: J14.5, J14.6, R11.1, U1.37 (IO23)
/ONEWIRE: J4.2, J5.2, R3.2, U1.12 (IO27)
/STEP: J14.7, R12.1, U1.30 (IO18)
/TACH_EXT: J3.3, R6.2, R7.1
/TEC_EN: J10.2, R10.1, U1.10 (IO25)
/U0RX: J11.3, U1.34 (RXD0/IO3)
/U0TX: J11.2, U1.35 (TXD0/IO1)
/UART_OEn: R14.2, U1.16 (IO13), U3.1, U4.1
/VMOT: C10.1, J1.1, J15.1, R18.1

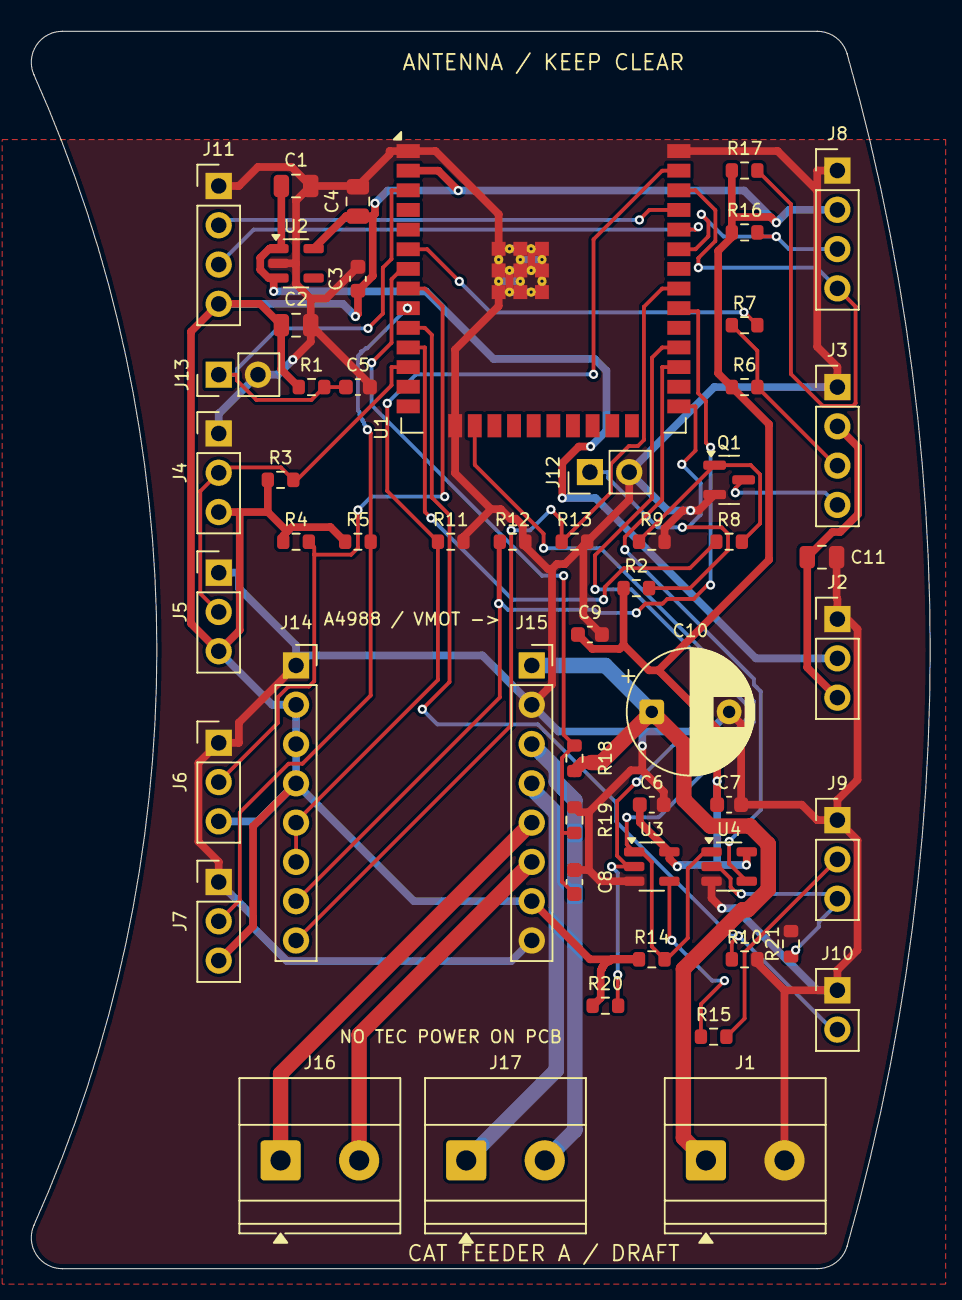
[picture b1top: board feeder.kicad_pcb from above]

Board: 2 copper layers, 58.1 x 80.0 mm, 54 parts (0 on the bottom side), 34 nets.

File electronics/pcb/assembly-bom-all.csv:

Comment,Designator,Footprint,LCSC Part #
ESP32-WROOM-32E-N4,U1,ESP32-WROOM-32E,C701341
AP2112K-3.3TRG1,U2,SOT-23-5,C51118
SN74LVC1G125DBVR,"U3,U4",SOT-23-5,C23654
MMBT3904,Q1,SOT-23,C20526
10k,"R1,R2,R4,R5,R6,R10,R11,R14,R19,R20,R21",R_0603_1608Metric,C25804
4.7k,"R3,R8,R16,R17",R_0603_1608Metric,C23162
1k,"R7,R15",R_0603_1608Metric,C21190
100k,"R9,R12,R13,R18",R_0603_1608Metric,C25803
10u 25V,"C1,C2,C4,C11",C_0805_2012Metric,C15850
100n,"C3,C6,C7,C8,C9",C_0603_1608Metric,C14663
1u 50V,C5,C_0603_1608Metric,C15849
100u 50V EEUFR1H101B,C10,CP_Radial_D8.0mm_P5.00mm,C713402
VMOT 20-24V INPUT,J1,"TerminalBlock_Phoenix_MKDS-1,5-2-5.08_1x02_P5.08mm_Horizontal",C5183929
RAILS GND-5V-12V,J2,PinHeader_1x03_P2.54mm_Vertical,C49257
FAN GND-12V-TACH-PWM,J3,PinHeader_1x04_P2.54mm_Vertical,C5116483
DS18B20 GND-DQ-3V3,"J4,J5",PinHeader_1x03_P2.54mm_Vertical,C49257
INDEX GND-SIG-3V3,J6,PinHeader_1x03_P2.54mm_Vertical,C49257
HOME GND-SIG-3V3,J7,PinHeader_1x03_P2.54mm_Vertical,C49257
I2C GND-3V3-SDA-SCL,J8,PinHeader_1x04_P2.54mm_Vertical,C5116483
DPS GND-RX-TX (DPS names),J9,PinHeader_1x03_P2.54mm_Vertical,C49257
TEC ENABLE GND-ON,J10,PinHeader_1x02_P2.54mm_Vertical,C27985187
PROG GND-TX-RX-3V3ref,J11,PinHeader_1x04_P2.54mm_Vertical,C5116483
BOOT short for download,J12,PinHeader_1x02_P2.54mm_Vertical,C27985187
RESET short to reset,J13,PinHeader_1x02_P2.54mm_Vertical,C27985187
A4988 CONTROL socket,J14,PinSocket_1x08_P2.54mm_Vertical,C27438
A4988 POWER socket,J15,PinSocket_1x08_P2.54mm_Vertical,C27438
MOTOR COIL1,J16,"TerminalBlock_Phoenix_MKDS-1,5-2-5.08_1x02_P5.08mm_Horizontal",C5183929
MOTOR COIL2,J17,"TerminalBlock_Phoenix_MKDS-1,5-2-5.08_1x02_P5.08mm_Horizontal",C5183929
